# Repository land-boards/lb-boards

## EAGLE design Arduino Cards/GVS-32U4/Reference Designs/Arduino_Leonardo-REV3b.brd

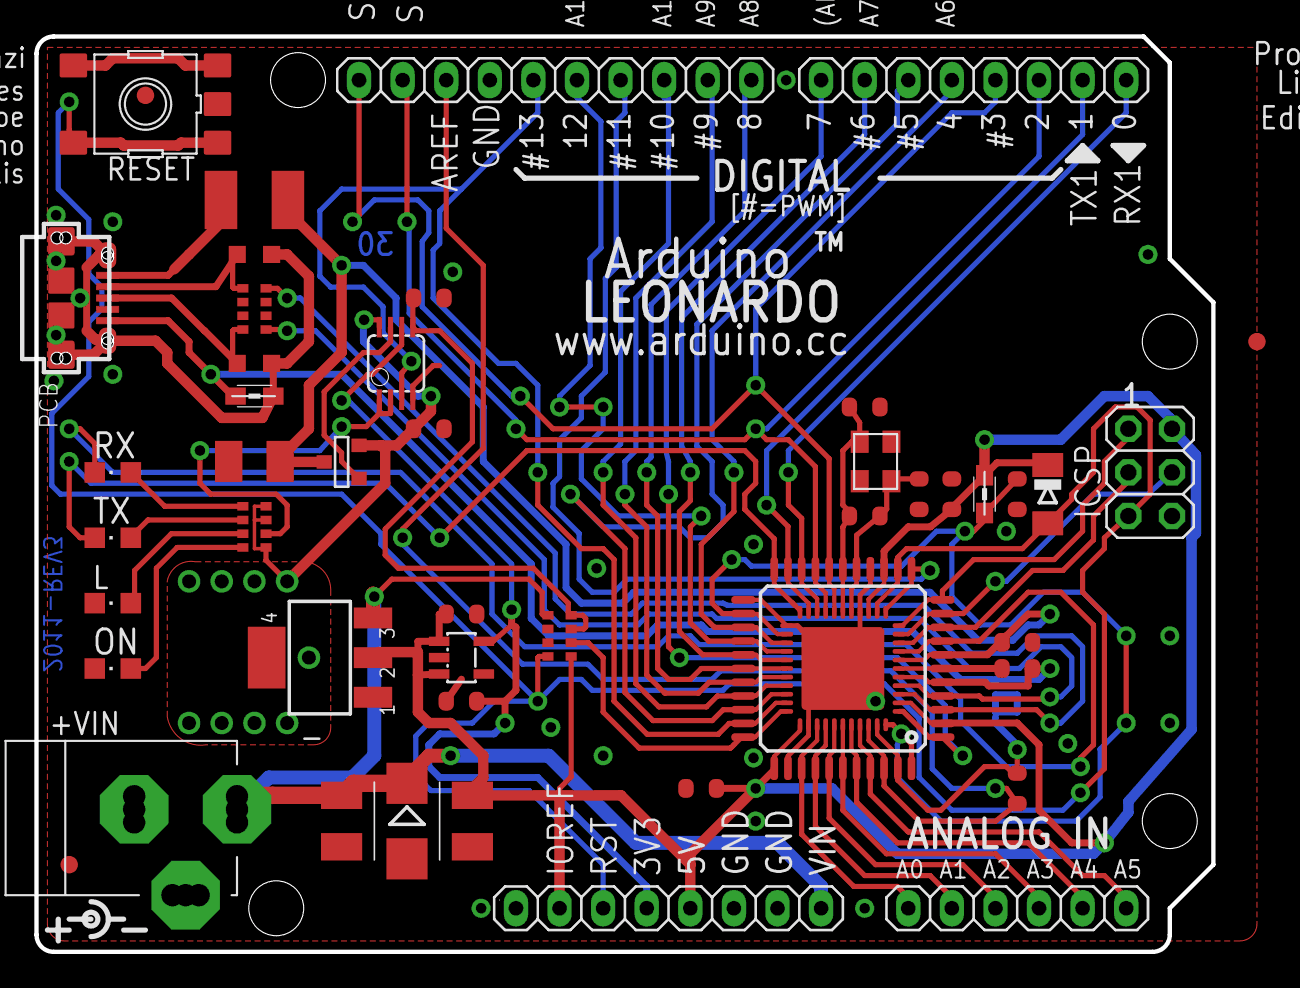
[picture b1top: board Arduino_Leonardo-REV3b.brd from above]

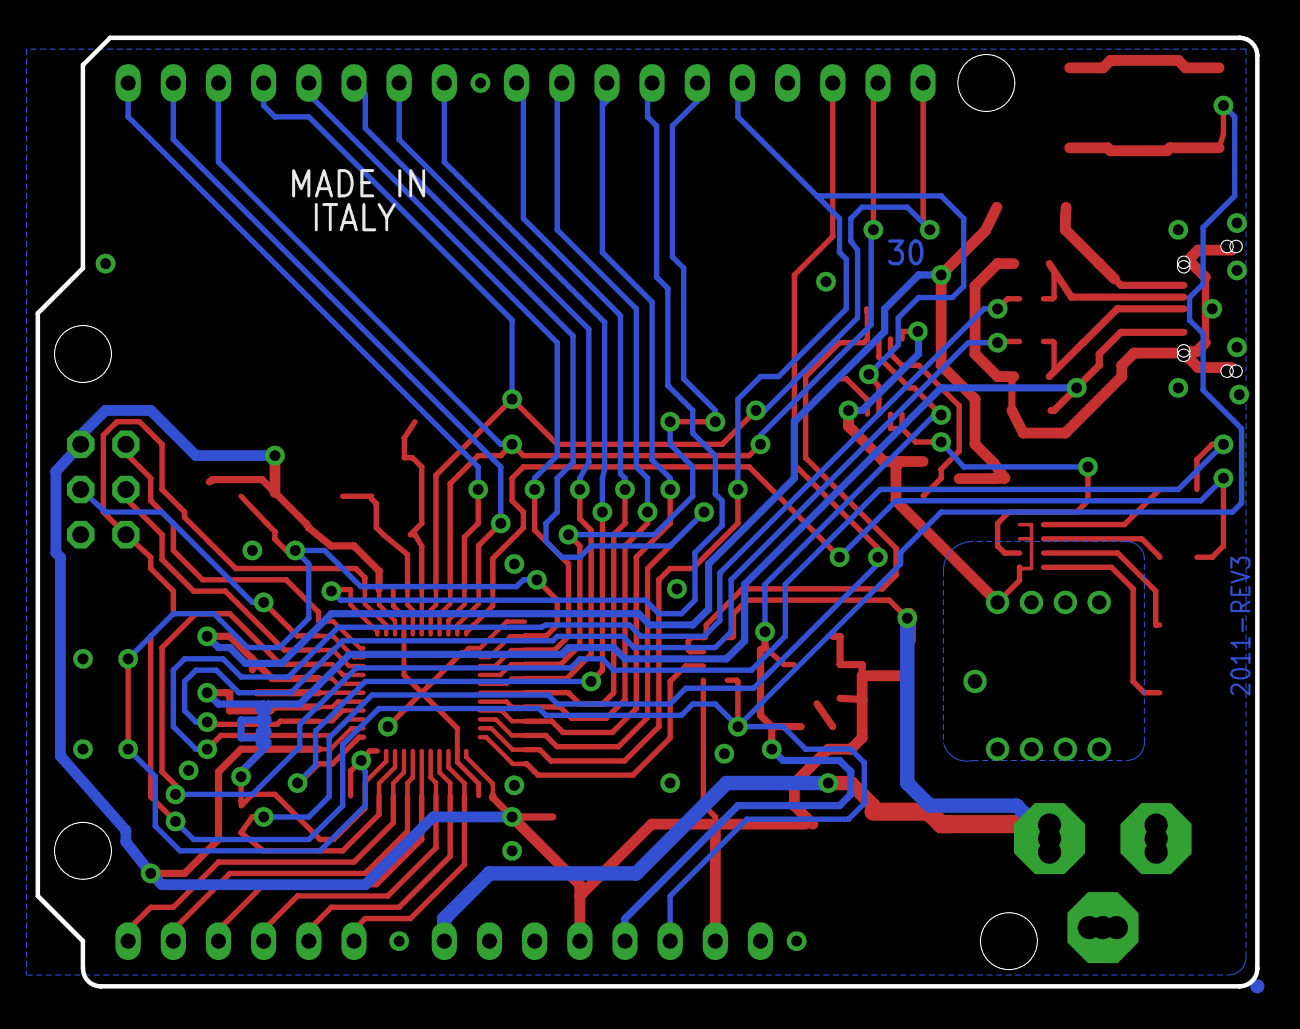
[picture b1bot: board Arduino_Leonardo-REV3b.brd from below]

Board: 2 copper layers, 68.6 x 53.3 mm, 51 parts (2 on the bottom side), 51 nets.

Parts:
C1, C2, C6, C9, C13, C22: 100n; C0603-ROUND
C3, C4: 22p; C0603-ROUND
C5, C7: 1uF; C0603-ROUND
C8, C10, C12: 10u; SMC_B
C11, C14: 1u; C0603-ROUND
D1: M7; SMB
D2: CD1206-S01575; MINIMELF
EXTPOWER: POWERSUPPLY_DC21MMX; POWERSUPPLY_DC-21MM
F1: MF-MSMF050-2 500mA; L1812
FID1, FID2, FID3: FIDUCIALMOUNT; FIDUCIA-MOUNT
IC1: NCP1117ST50T3G; SOT223
IC2: LMV358IDGKR; MSOP08
ICSP: ICSP; 2X03
J1: USB MICRO; CON2_USB_MICRO_B_AT
J2, J3: 8x1F-H8.5; 1X08
J4: 6x1F-H8.5; 1X06
JP1: 10x1F-H8.5; 1X10
L: Yellow; CHIPLED_0805
L1, L2: MH2029-300Y; 0805
ON: Green; CHIPLED_0805
ORIGIN: TP_SP; TP-SP
R1: 1M; R0603-ROUND
R2, R3: NM; R0402
RESET: TS42
RN1: 10K; CAY16
RN2: 1K; CAY16
RN3: 22R; CAY16
RX: Yellow; CHIPLED_0805
T1: FDN340P; SOT-23
TX: Yellow; CHIPLED_0805
U1: ATMEGA32U4-XUMU; QFN44ML7X7
U2: ATMEGA32U4-XUAU; TQFP44-PAD
U3: LP2985-33DBVR; SOT23-DBV
Y1: 16MHz KX-7; CRYSTAL-3.2-2.5
Z1, Z2: CG0603MLC-05E; CT/CN0603

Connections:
+3V3: C14.2, IC2.6, J3.4, U3.5
+5V: C1.1, C2.1, C11.2, C12.+, C13.1, D2.C, IC1.2, IC1.4, IC2.8, ICSP.2, J3.2, J3.5, L1.1, RN1.5, RN2.1, RN2.3, RN2.4, T1.2, U1.2, U1.14, U1.34, U2.2, U2.14, U2.34, U3.1, U3.3
A0: J4.1, U1.36, U2.36
A1: J4.2, U1.37, U2.37
A2: J4.3, U1.38, U2.38
A3: J4.4, U1.39, U2.39
A4: J4.5, U1.40, U2.40
A5: J4.6, U1.41, U2.41
AGND: C6.1, R2.1, U1.43, U2.43
AREF: C6.2, JP1.8, U1.42, U2.42
AVCC: C5.1, L1.2, U1.24, U1.44, U2.24, U2.44
CMP: C22.2, IC2.5, RN1.7, RN1.8
D0/RX: J2.1, U1.20, U2.20
D1/TX: J2.2, U1.21, U2.21
D2/SDA: J2.3, JP1.9, U1.19, U2.19
D3/SCL: J2.4, JP1.10, U1.18, U2.18
D4: J2.5, U1.25, U2.25
D5*: J2.6, U1.31, U2.31
D6*: J2.7, U1.27, U2.27
D7: J2.8, U1.1, U2.1
D+: J1.P3, RN3.8, Z1.1
D-: J1.P2, RN3.5, Z2.1
GATE_CMD: IC2.7, T1.3
GND: C1.2, C2.2, C3.1, C4.2, C5.2, C8.-, C9.1, C10.-, C11.1, C12.-, C13.2, C14.1, C22.1, D1.A, EXTPOWER.1, EXTPOWER.3, IC1.1, IC2.4, ICSP.6, J1.S1, J1.S2, J1.S3, J1.S4, J1.S5, J1.S6, J3.6, J3.7, JP1.7, L.C, L2.2, ON.C, R2.2, R3.1, RESET.3, RESET.4, RN1.2, RN1.3, U1.15, U1.23, U1.35, U1.EXP, U2.15, U2.23, U2.35, U2.P$1, U3.2, Y1.2, Y1.4, Z1.2, Z2.2
HWB: RN1.6, U1.33, U2.33
IO8: JP1.1, U1.28, U2.28
IO9*: JP1.2, U1.29, U2.29
IO10*: JP1.3, U1.30, U2.30
IO11*: JP1.4, U1.12, U2.12
IO12: JP1.5, U1.26, U2.26
IO13*: IC2.3, JP1.6, U1.32, U2.32
LL: IC2.1, IC2.2, RN2.2
MISO: ICSP.1, U1.11, U2.11
MOSI: ICSP.4, U1.10, U2.10
unnamed: L.A, RN2.7
unnamed: ON.A, RN2.8
unnamed: RN2.6, TX.A
unnamed: RN2.5, RX.A
RD+: RN3.1, U1.4, U2.4
RD-: RN3.4, U1.3, U2.3
RESET: D2.A, ICSP.5, J3.3, RESET.1, RESET.2, RN1.4, U1.13, U2.13
RXLED: RX.C, U1.8, U2.8
SCK: ICSP.3, U1.9, U2.9
TXLED: TX.C, U1.22, U2.22
UCAP: C7.1, U1.6, U2.6
UGND: C7.2, J1.P5, L2.1, R3.2, U1.5, U2.5
VIN: C10.+, D1.C, EXTPOWER.2, IC1.3, J3.8, RN1.1
VUSB: C8.+, C9.2, F1.1, T1.1, U1.7, U2.7
XTAL1: C4.1, R1.1, U1.17, U2.17, Y1.1
XTAL2: C3.2, R1.2, U1.16, U2.16, Y1.3
XUSB: F1.2, J1.P1
